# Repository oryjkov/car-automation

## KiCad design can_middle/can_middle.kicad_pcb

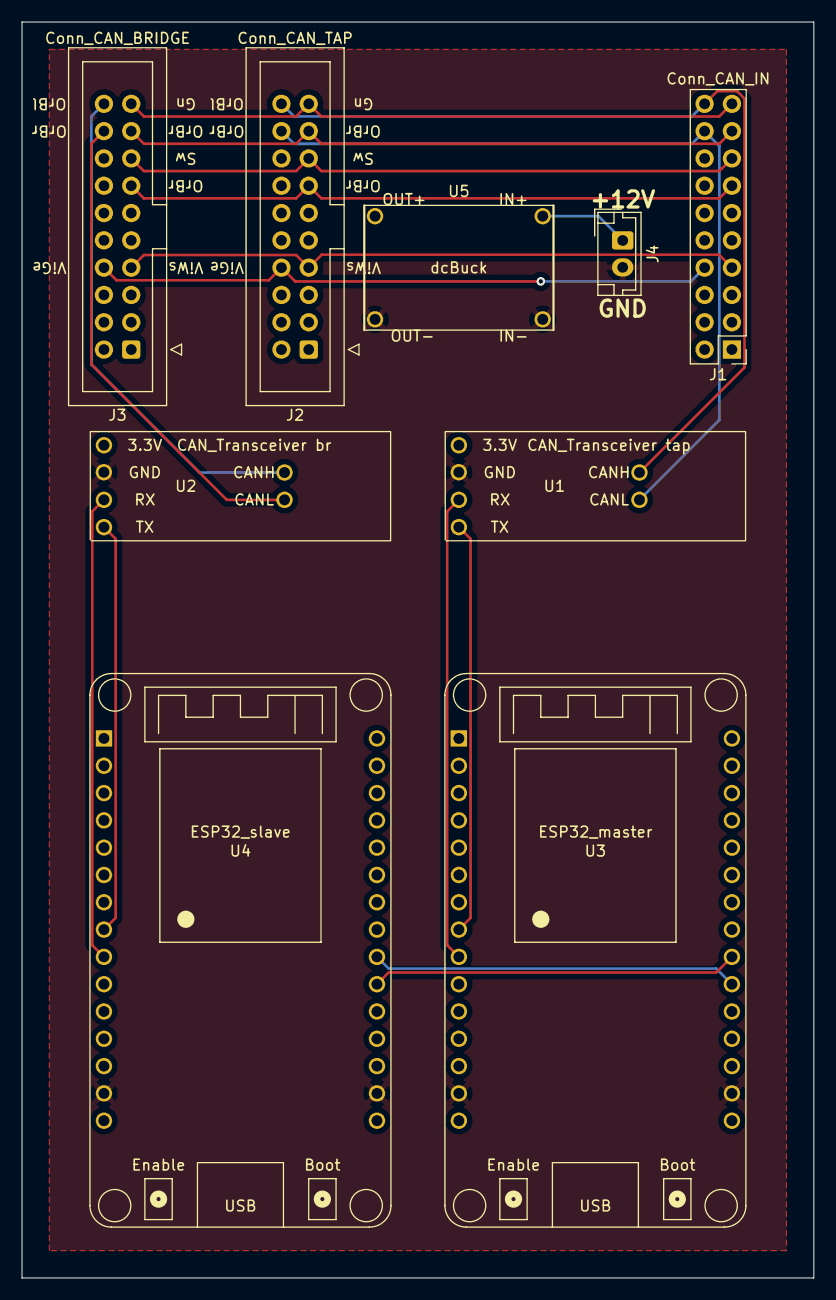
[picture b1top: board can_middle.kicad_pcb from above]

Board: 2 copper layers, 73.7 x 116.8 mm, 9 parts (0 on the bottom side), 19 nets.

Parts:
J1: Conn_CAN_IN; PinHeader_2x10_P2.54mm_Vertical
J2: Conn_CAN_TAP; VW T20d connector
J3: Conn_CAN_BRIDGE; VW T20d connector
J4: Conn_01x02; JST_EH_B2B-EH-A_1x02_P2.50mm_Vertical
U1: CAN_Transceiver tap; CAN_Transciever
U2: CAN_Transceiver br; CAN_Transciever
U3: ESP32_master; esp32_devkit_v1_doit
U4: ESP32_slave; esp32_devkit_v1_doit
U5: dcBuck; dcbuck

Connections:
+3.3V: U1.4 (3.3V), U2.4 (3.3V), U3.16 (3V3), U4.16 (3V3), U5.4 (OUT+)
+12V: J4.1, U5.3 (IN+)
/MASTER-RX: U3.21 (RX2/IO16), U4.22 (TX2/IO17)
/MASTER-TX: U3.22 (TX2/IO17), U4.21 (RX2/IO16)
/MASTER_CAN_RX: U1.1 (TX), U3.8 (IO25)
/MASTER_CAN_TX: U1.2 (RX), U3.9 (IO26)
/SLAVE_CAN_RX: U2.1 (TX), U4.8 (IO25)
/SLAVE_CAN_TX: U2.2 (RX), U4.9 (IO26)
/a1: J1.19, J2.19, J3.19
/a2: J1.17, J2.17, J3.17
/a3: J1.15, J2.15, J3.15
/a4: J1.13, J2.13, J3.13
/a7: J1.7, J2.7, J3.7
/a11_EXT_CANH: J1.20, J2.20, U1.6 (CANH)
/a12_EXT_CANL: J1.18, J2.18, U1.5 (CANL)
/a17: J1.8, J2.8, J3.8
/b11_EXT_CANH: J3.20, U2.6 (CANH)
/b12_EXT_CANL: J3.18, U2.5 (CANL)
GND: J4.2, U1.3 (GND), U2.3 (GND), U3.14 (GND), U3.17 (GND), U4.14 (GND), U4.17 (GND), U5.1 (OUT-), U5.2 (IN-)

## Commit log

2022-06-17 config for the victron mppt
2022-06-17 flash command
2022-06-21 working now
2022-06-21 8255
2022-06-22 daly configs and debug logs
2022-06-22 split config and rename
2022-06-22 reip
2022-06-23 Switched to use the hardware serial linewq
2022-06-23 remove unused sensors
2022-09-08 added the status led
2022-09-08 removed debug logs
2022-09-08 secrets
2022-09-08 remove logs
2022-09-21 ESP CAN config that exposes the fridge status
2022-09-21 Refresh added
2022-09-28 restart button for espcan
    It hanged up after some time.
2022-09-30 zigbee bridge
2022-09-30 re ip
2022-10-09 pcb for can in the middle
2022-10-09 layed out
2022-10-09 removed unused
2022-10-09 cleanups before printing
2022-10-20 forwarding sw
2022-10-20 nanopb and master/slave programming
2022-10-20 can over serial send working
2022-10-21 added another role, implementation of can-serial sw
2022-10-21 bypass is working in the van
    changes:
    1. removed detailed logging from master+slave roles
    2. added mirror role that mirrors traffic back
    3. added stats counting and printing
    tested in the van. There were a few errors during on the serial link,
    but it worked well enough to show the display in the car
2022-10-22 parallel upload to several devices
2022-10-22 Send on both sides, on side mirrors.
    stats on master
    [00070015] can: tx/err tx, rx/err rx: 22158/42, 57071/0, ser: tx/err tx, rx/err rx: 57071/0, 26173/4015
2022-10-22 typo
2022-10-22 Serial protocol with one-way initiation
    not working so far, slave is not reading all the data.
2022-10-22 fixed CAN chip comms to make it work on rev 2+ esp32 chips
2022-10-22 One way serial comm working in the harness
    [00120062] can: tx/err tx, rx/err rx: 57606/122, 57697/0, ser: tx/err tx, rx/err rx: 57698/0, 57698/1 sl drops: 0
    not tested in the car yet
2022-10-22 randomized messages
2022-10-23 unit test using a loopback serial esp32
2022-10-23 remove a debug statement
    also set faster serial speed to stress test
2022-10-23 stupid bug printing junk for extended frames
    together with a bug that was not testing exteded frames :(
2022-10-23 moved proto paths
2022-10-23 buffer with multiple messages
2022-10-24 fix sending of long messages (>256 bytes)
    tests
2022-10-24 secret
2022-10-25 Added webserver and snooping
    jupyter notebook to snoop
2022-10-25 fix slave snooping
2022-10-25 ignore pyc
2022-10-25 remove pyc
2022-10-26 snooped data from canbus
    snoop2 seems more complete, also includes turning on the light above the
    sliding door
2022-10-26 blink slave led on activity
2022-10-26 improve stats
2022-10-26 clangformat
2022-10-26 stack trace parser
2022-10-26 major rewrite
    1. use the esp idf can driver instead of arduino can.
    2. full duplex serial mode, also using the ESP driver instead of arduino
2022-10-26 new dump
2022-10-27 Transmit queues for UART and CAN
    tested with the two sided CAN
    Speeds: 248 / 346 pkt/sec. Not much different from before.
    Idea is that this will make it easier to add additional message
    processing tasks.
2022-10-28 Introduced the model class
    Model class sits between tx and rx. Model sends state update and
    can be updated from the car/display via can messages.
    Moved TX to separate queues.
    Made snoop buffer locking.
    Snoop tx and RX on both directions.
    googletest native tests for the model.
2022-10-28 send/receive timing that looks like on the car
2022-10-28 auto start
2022-10-28 Tested with the car.
    comms via the model are working! display sees the old state when
    connected to the board without a car connection.
    When car and display are both connected, then light controls work.
    also fixed the STOP command from looping. This needs a better approach.
2022-10-28 Comments. Named a constant.
2022-10-30 helper to run a task in background
    fns to toggle lights
2022-10-30 fix 2 bugs
    slave should simply passthrough packets.
    snoop in slave was getting a segfault since it is not initialized.
2022-10-30 Light controls including brightness
    Not all works, known problems are:
    - The last light that was turned on via the API can't be controlled with
    its physical button
    - If a light was turned on with its button then it can't be controlled
    via the API.
    for the first issue - the car display addresses it by reacting to the
2022-10-30 hack in propery display filtering
2022-10-31 added the mqtt client
2022-10-31 configure 'passthrough' to be able to just snoop
2022-10-31 traffic dump from another t6.1
2022-10-31 Replaced web handlers with mqtt
2022-10-31 dump a few separate libraries together to make it compile
    The libraries are getting messy. This probably breaks native tests, but
    for now it lets me get mqtt updates happening.
2022-10-31 Handle property updates for lights report to mqtt
2022-10-31 light descriptors for control
2022-11-01 not used
2022-11-01 comment
2022-11-01 tests are compiling and passing.
    The model must have been getting "comtaminated" by a non-native
    dependency and PIO was ignoring to include it.
2022-11-01 added a missing include
2022-11-01 hass config
2022-11-01 mqtt discovery - not tested
2022-11-02 tested discovery, added buttons
2022-11-02 fridge control
2022-11-02 added unique id, fix setting brightness.
2022-11-02 lights enum
2022-11-02 needed to compile the webauth library
2022-11-02 ota update
2022-11-02 change mqtt broker
2022-11-04 rm unused config
2022-11-04 Refactor TWAI+UART TX and RX into its own class
2022-11-04 Pulled out the snoop buffer, log props
    Properties are logged, but not possible to retrieve yet. Also not
    tested.
2022-11-15 system diagram
2022-11-15 Split lock and enqueue to separate classes
2022-11-15 props logger and snoop buffer do not depend on HW
2022-11-15 tests for snoop buffer
2022-11-15 tests for props logger
2022-11-15 handler to get props
2022-11-15 separate test main
2022-11-15 follow up to the last commit
2022-11-15 rollover when full
2022-11-16 pins
2022-11-16 fixes after uploading the new fw
2022-11-25 On/Off mosfet toggle for daly bms
    hacked via a UART switch
2023-01-13 Configs for setting up the car android with homeassistant
    run_docker.sh - runs the docker daemon, needs to run manually on startup
    update_hass.sh updates and runs the home assistant container.
2023-01-13 led strip
2023-01-15 Remove static IP and enable serial output on uart1
2023-01-15 Split the leds into 2.
    Home assistant does not show the RGB spectrum conrol for the RGBCW
    light, but does for RGB.
2023-01-16 renamed the color components
2023-01-16 Updates to run with the dynamic ip
    As the phone changes the subnet of its tethering IP range on every boot,
    I can not get away with the static IPs. Hence using dynamic IPs here.
    Note that it requires HASS to have a working SSDP setup. In particular
    this means configuring the multicast interface to be wlan1, which
    happens to be the tethering interface used on lineageos.
    Further I changed the logger to output to GPIO2 which is UART1 on
2023-01-16 New setup script
    Added sv launchers for:
    - Docker
    - wifi tethering
    wifi tethering is just a one-off command, but I'm plugging it into sv
    startup so that it runs at the first unlock.
2023-01-19 Owntracks to report location
2023-01-19 fix python errors
2023-01-19 unused now
2023-01-19 shorter device names
2023-01-19 switch car ha to influxdb
2024-07-10 unlock huawei 4g modem
2024-07-10 gone
2024-07-10 basic comms with daly bms
2024-07-10 use floats and fns, checksum
2024-07-10 mqtt dep
2024-07-12 mqtt added and using socat to test
    HA is not happy yet, but it gets the discovery message
2024-07-12 Added battery current sensor and hass discovery works now
2024-07-12 sensor updates
2024-07-12 Two more sensors
2024-07-12 temperature sensor
2024-07-12 charge/discharge switches work
2024-07-12 send messages again
2024-07-12 Use a logger package
2024-07-12 (somewhat) Generic mqtt entities
2024-07-12 Send mqtt discover messages when the loop is runnging
    otherwise it hangs when there are more than 10 messages
2024-07-12 Beefed up the decoded for handling consecutive messages
2024-07-12 nicer icons
